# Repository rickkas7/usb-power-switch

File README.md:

# USB Power Switch

*Simple board that disconnects power from a USB connection while maintaining data and GND*

On the Argon and Xenon Particle boards in particular, it's not a good idea to power by USB and the VUSB pin at the same time, as there is no protection diode to prevent power from your power supply from affecting the USB, or vice versa.

While power-only USB cables are common, data-only cables are not. I made this little board to allow the power to be easily disconnected. 

## BOM

| Description | Example |
| --- | --- |
| CONN USB MICRO B RECPT SMT R/A | [Amphenol FCI 10118194-0001LF](https://www.digikey.com/products/en?keywords=609-4618-1-nd) |
| USB-A Receptacle | [Amphenol 87520-0010BLF](https://www.digikey.com/products/en?keywords=609-1045-ND) |
| SWITCH SLIDE SPDT 200MA 30V | [E-Switch EG1218](https://www.digikey.com/product-detail/en/e-switch/EG1218/EG1903-ND/101726) |
| Green 572nm LED 2V 5 mA 0603 | [Lite-On LTST-C193KGKT-5A](https://www.digikey.com/product-detail/en/lite-on-inc/LTST-C193KGKT-5A/160-1828-1-ND/2356247) |
| RES SMD 680 OHM 5% 1/8W 0805 | [Panasonic ERJ-6GEYJ681V](https://www.digikey.com/product-detail/en/panasonic-electronic-components/ERJ-6GEYJ681V/P680ACT-ND/90033) |

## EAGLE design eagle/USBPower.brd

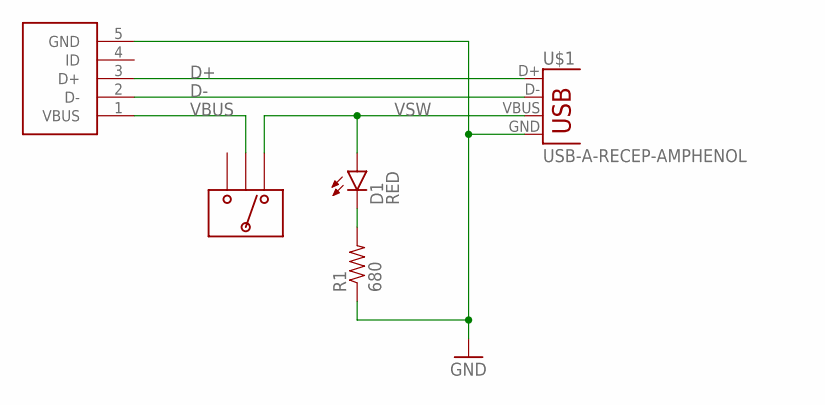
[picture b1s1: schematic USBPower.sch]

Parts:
D1: RED; LED-0603
R1: 680; 0805
U$1: USB-A-RECEP-AMPHENOL
U$2: USB-MICRO-B-SOCKET-AMPHENOL; USB-B-SMT-AMPHENOL
U$3: SWITCH-SLIDE-SPDT-TH

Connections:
D+: U$1.D+, U$2.3 (D+)
D-: U$1.D-, U$2.2 (D-)
GND: R1.1, U$1.GND, U$2.5 (GND)
unnamed: D1.C, R1.2
VBUS: U$2.1 (VBUS), U$3.2
VSW: D1.A, U$1.VBUS, U$3.1

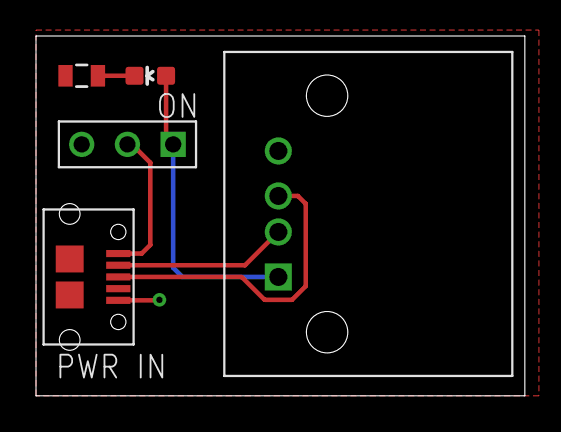
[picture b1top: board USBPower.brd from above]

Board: 2 copper layers, 27.2 x 20.0 mm, 5 parts (0 on the bottom side), 6 nets.
